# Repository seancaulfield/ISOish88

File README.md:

ISO(ish)88
==========

h88-compatible, F13 TKL with ISO support first (and no ANSI support)

* Uses RP2040 as microcontroller
* Hotswap supported
* Split left and right shift keys
* Bottom row is 7u/Tsangan (only, no ANSI support)

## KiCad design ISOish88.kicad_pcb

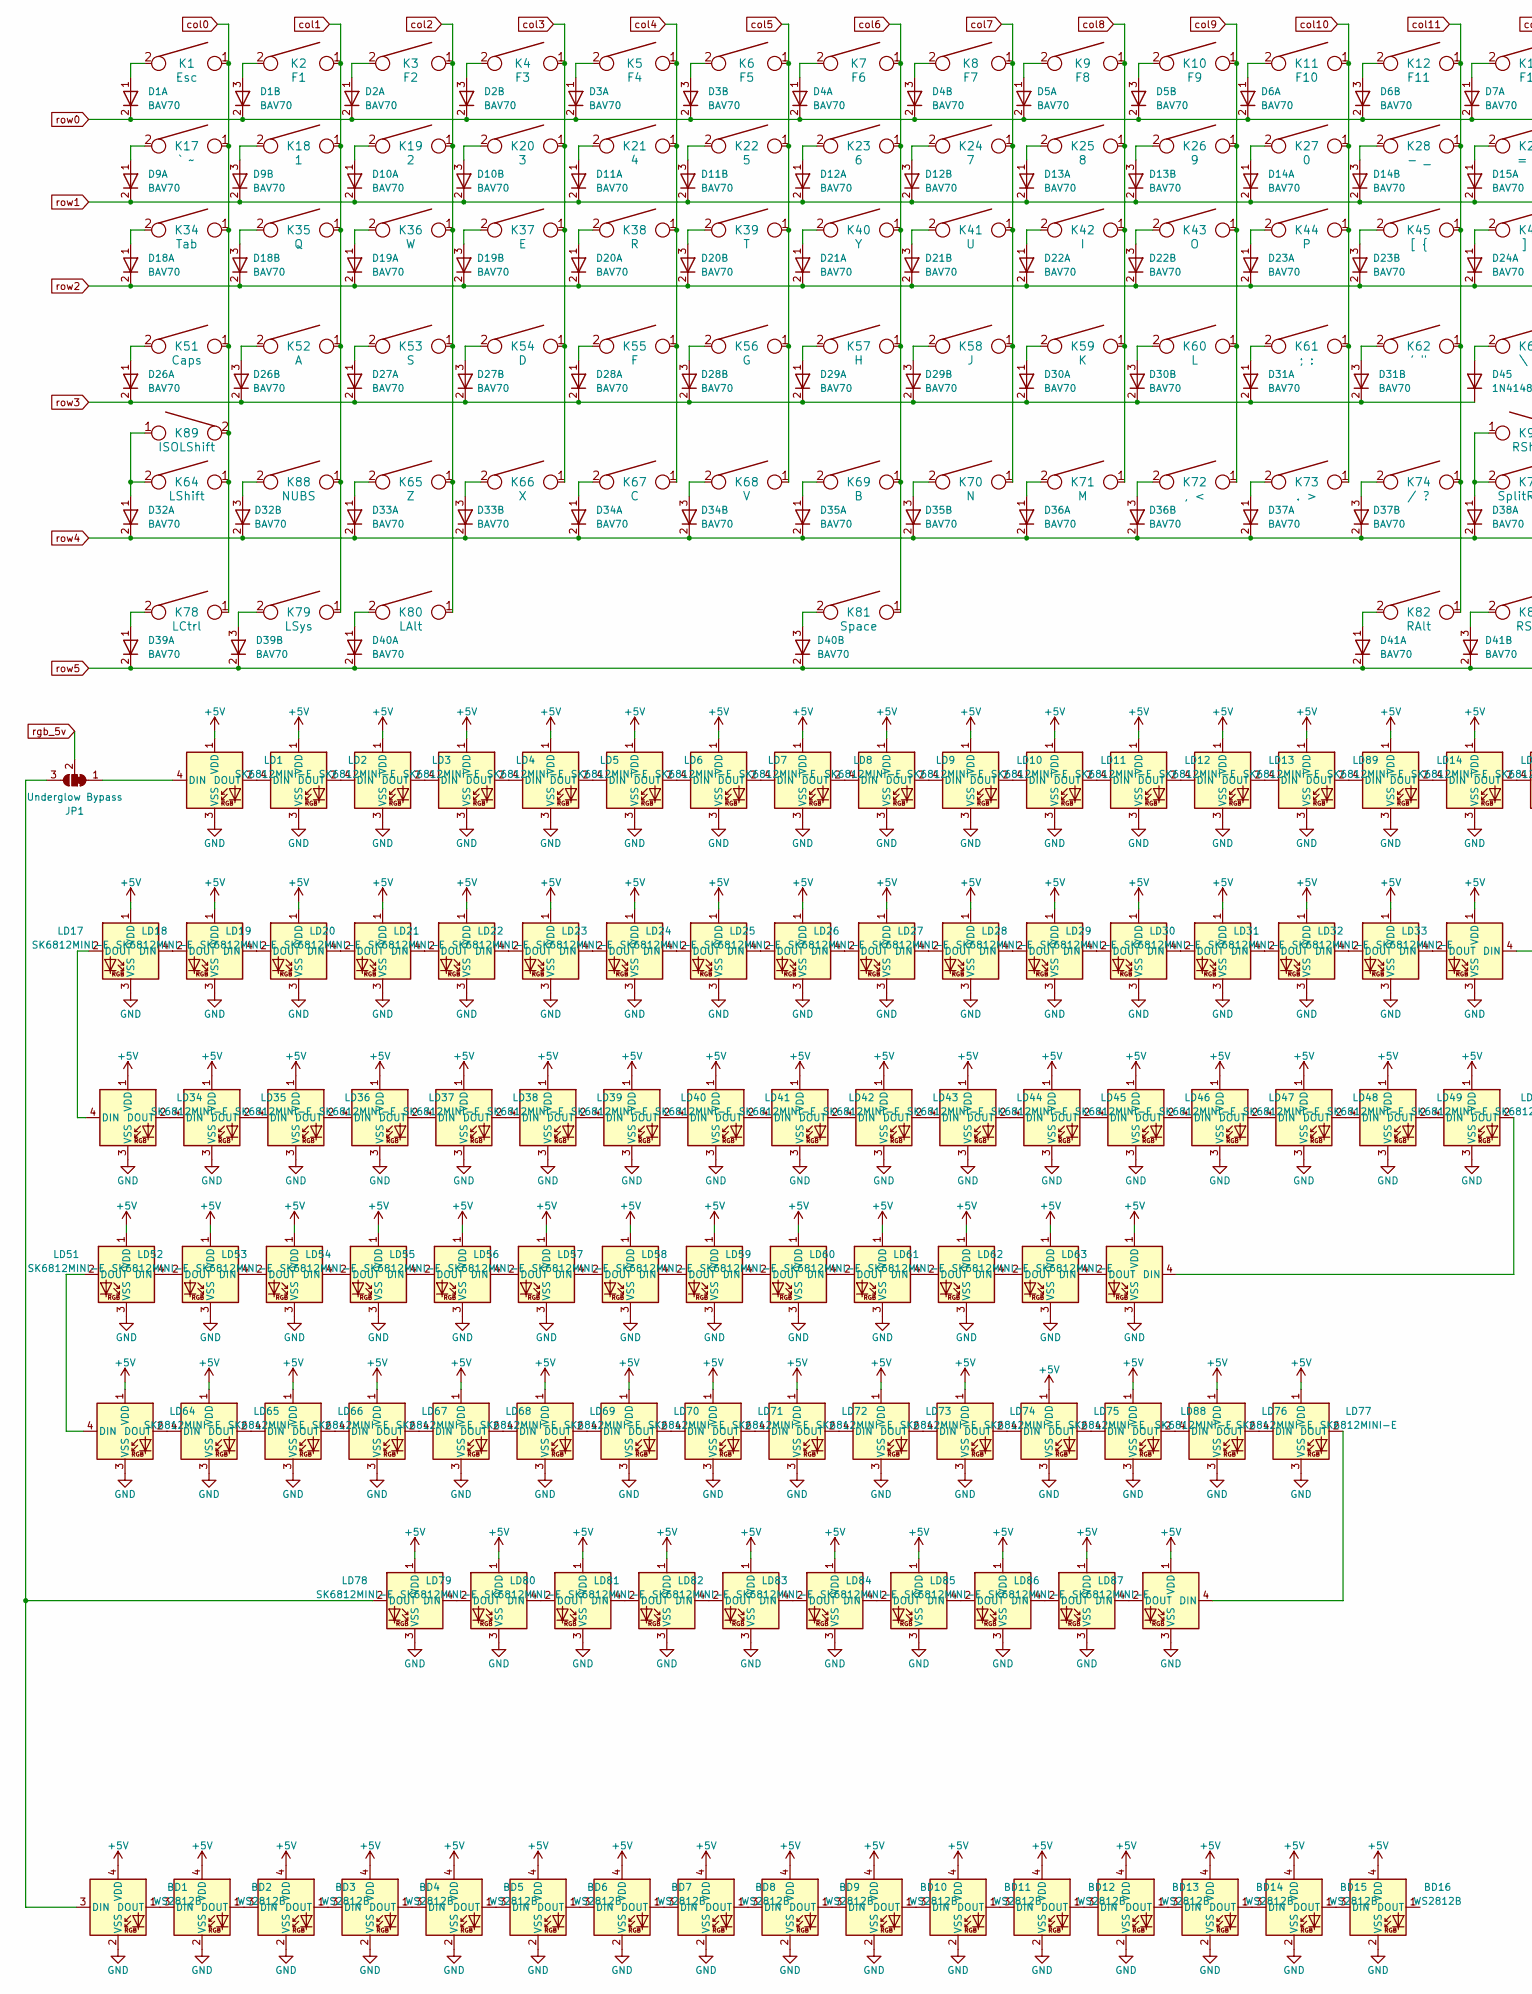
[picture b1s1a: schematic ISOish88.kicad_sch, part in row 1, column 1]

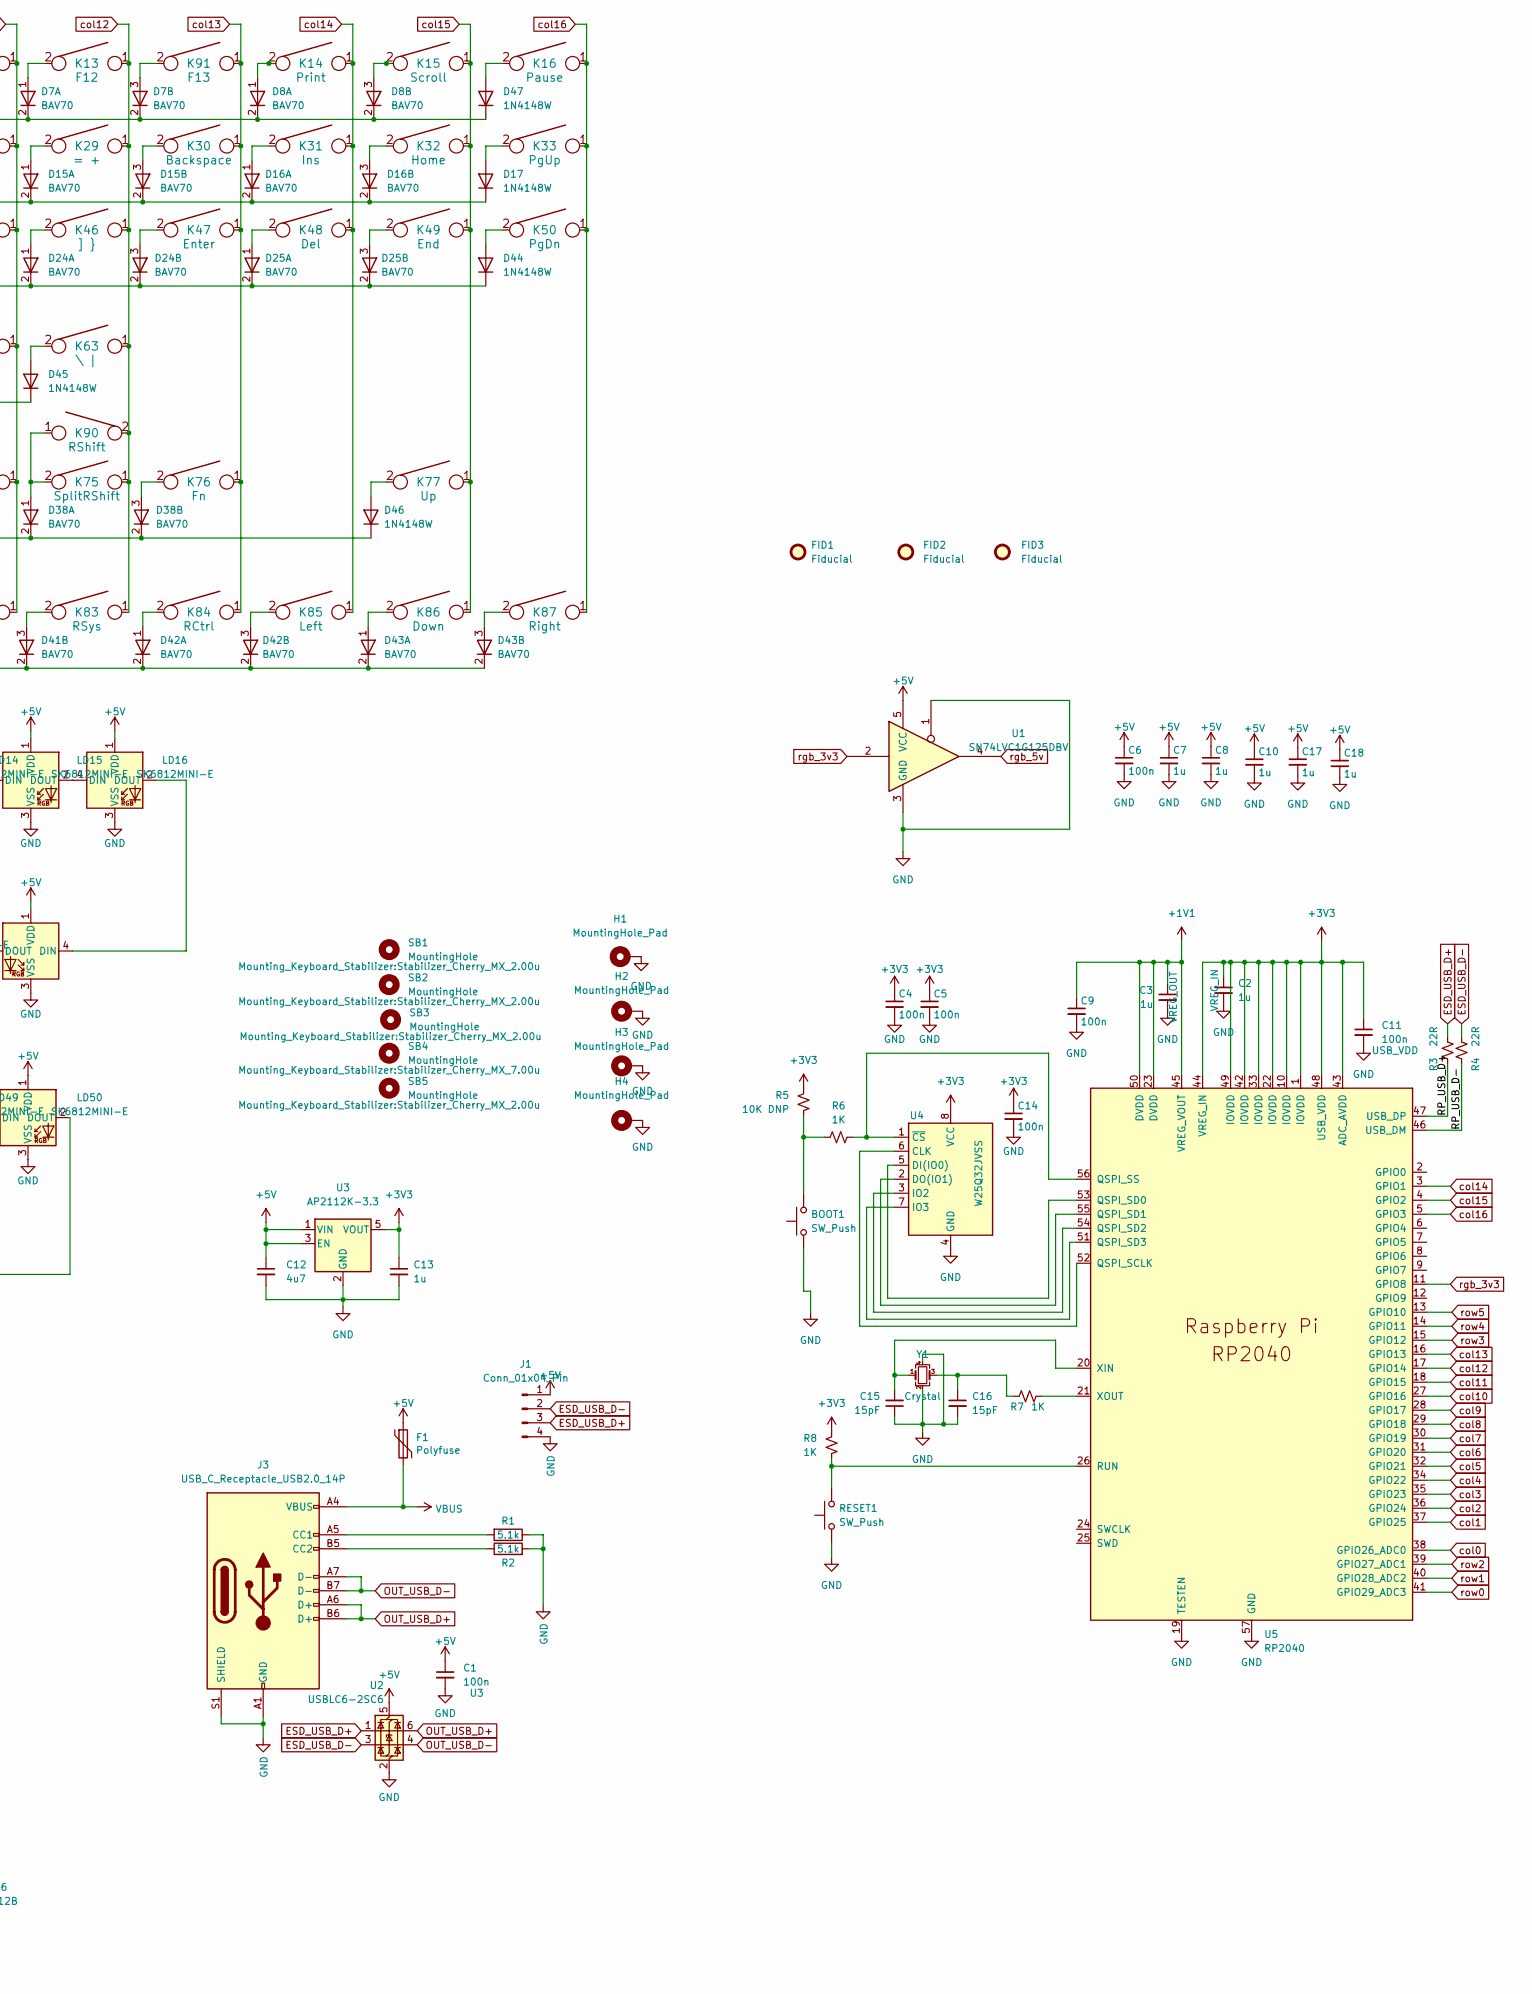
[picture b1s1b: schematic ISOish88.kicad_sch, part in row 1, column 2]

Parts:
BD1, BD2, BD3, BD4, BD5, BD6, BD7, BD8, BD9, BD10, BD11, BD12, BD13, BD14, BD15, BD16: WS2812B; LED_SK6812MINI_PLCC4_3.5x3.5mm_P1.75mm
BOOT1: SW_Push; SW_SPST_SKQG_WithStem
C1, C4, C5, C6, C9, C11, C14: 100n; C_0603_1608Metric
C2, C3, C7, C8, C10, C13, C17, C18: 1u; C_0603_1608Metric
C12: 4u7; C_0805_2012Metric
C15, C16: 15pF; C_0603_1608Metric
D1, D2, D3, D4, D5, D6, D7, D8, D9, D10, D11, D12, D13, D14, D15, D16, D18, D19, D20, D21, D22, D23, D24, D25, D26, D27, D28, D29, D30, D31, D32, D33, D34, D35, D36, D37, D38, D39, D40, D41, D42, D43: BAV70; SOT-23-1-3-2
D17, D44, D45, D46, D47: 1N4148W; D_SOD-123
F1: Polyfuse; R_1206_3216Metric
FID1: Fiducial; qmk_logo
FID2: Fiducial; OSHW-Logo_5.7x6mm_SilkScreen
FID3: Fiducial; COW
H1, H2, H3, H4: MountingHole_Pad; MountingHole_3.0mm_M2_5mm_dia_solderable
J1: Conn_01x04_Pin; JST_SH_SM04B-SRSS-TB_1x04-1MP_P1.00mm_Horizontal
J3: USB_C_Receptacle_USB2.0_14P; USB_C_Receptacle_GCT_USB4105-xx-A_16P_TopMnt_Horizontal
JP1: Underglow Bypass; SolderJumper-3_P1.3mm_Bridged12_RoundedPad1.0x1.5mm
K1: Esc; SW_Hotswap_Kailh_MX_1.00u
K2: F1; SW_Hotswap_Kailh_MX_1.00u
K3: F2; SW_Hotswap_Kailh_MX_1.00u
K4: F3; SW_Hotswap_Kailh_MX_1.00u
K5: F4; SW_Hotswap_Kailh_MX_1.00u
K6: F5; SW_Hotswap_Kailh_MX_1.00u
K7: F6; SW_Hotswap_Kailh_MX_1.00u
K8: F7; SW_Hotswap_Kailh_MX_1.00u
K9: F8; SW_Hotswap_Kailh_MX_1.00u
K10: F9; SW_Hotswap_Kailh_MX_1.00u
K11: F10; SW_Hotswap_Kailh_MX_1.00u
K12: F11; SW_Hotswap_Kailh_MX_1.00u
K13: F12; SW_Hotswap_Kailh_MX_1.00u
K14: Print; SW_Hotswap_Kailh_MX_1.00u
K15: Scroll; SW_Hotswap_Kailh_MX_1.00u
K16: Pause; SW_Hotswap_Kailh_MX_1.00u
K17: ` ~; SW_Hotswap_Kailh_MX_1.00u
K18: 1; SW_Hotswap_Kailh_MX_1.00u
K19: 2; SW_Hotswap_Kailh_MX_1.00u
K20: 3; SW_Hotswap_Kailh_MX_1.00u
K21: 4; SW_Hotswap_Kailh_MX_1.00u
K22: 5; SW_Hotswap_Kailh_MX_1.00u
K23: 6; SW_Hotswap_Kailh_MX_1.00u
K24: 7; SW_Hotswap_Kailh_MX_1.00u
K25: 8; SW_Hotswap_Kailh_MX_1.00u
K26: 9; SW_Hotswap_Kailh_MX_1.00u
K27: 0; SW_Hotswap_Kailh_MX_1.00u
K28: - _; SW_Hotswap_Kailh_MX_1.00u
K29: = +; SW_Hotswap_Kailh_MX_1.00u
K30: Backspace; SW_Hotswap_Kailh_MX_2.00u
K31: Ins; SW_Hotswap_Kailh_MX_1.00u
K32: Home; SW_Hotswap_Kailh_MX_1.00u
K33: PgUp; SW_Hotswap_Kailh_MX_1.00u
K34: Tab; SW_Hotswap_Kailh_MX_1.50u
K35: Q; SW_Hotswap_Kailh_MX_1.00u
K36: W; SW_Hotswap_Kailh_MX_1.00u
K37: E; SW_Hotswap_Kailh_MX_1.00u
K38: R; SW_Hotswap_Kailh_MX_1.00u
K39: T; SW_Hotswap_Kailh_MX_1.00u
K40: Y; SW_Hotswap_Kailh_MX_1.00u
K41: U; SW_Hotswap_Kailh_MX_1.00u
K42: I; SW_Hotswap_Kailh_MX_1.00u
K43: O; SW_Hotswap_Kailh_MX_1.00u
K44: P; SW_Hotswap_Kailh_MX_1.00u
K45: [ {; SW_Hotswap_Kailh_MX_1.00u
K46: ] }; SW_Hotswap_Kailh_MX_1.00u
K47: Enter; SW_Hotswap_Kailh_MX_ISOEnter
K48: Del; SW_Hotswap_Kailh_MX_1.00u
K49: End; SW_Hotswap_Kailh_MX_1.00u
K50: PgDn; SW_Hotswap_Kailh_MX_1.00u
K51: Caps; SW_Hotswap_Kailh_MX_1.25u
K52: A; SW_Hotswap_Kailh_MX_1.00u
K53: S; SW_Hotswap_Kailh_MX_1.00u
K54: D; SW_Hotswap_Kailh_MX_1.00u
K55: F; SW_Hotswap_Kailh_MX_1.00u
K56: G; SW_Hotswap_Kailh_MX_1.00u
K57: H; SW_Hotswap_Kailh_MX_1.00u
K58: J; SW_Hotswap_Kailh_MX_1.00u
K59: K; SW_Hotswap_Kailh_MX_1.00u
K60: L; SW_Hotswap_Kailh_MX_1.00u
K61: ; :; SW_Hotswap_Kailh_MX_1.00u
K62: ' "; SW_Hotswap_Kailh_MX_1.00u
K63: \ |; SW_Hotswap_Kailh_MX_1.00u
K64: LShift; SW_Hotswap_Kailh_MX_2.25u
K65: Z; SW_Hotswap_Kailh_MX_1.00u
K66: X; SW_Hotswap_Kailh_MX_1.00u
K67: C; SW_Hotswap_Kailh_MX_1.00u
K68: V; SW_Hotswap_Kailh_MX_1.00u
K69: B; SW_Hotswap_Kailh_MX_1.00u
K70: N; SW_Hotswap_Kailh_MX_1.00u
K71: M; SW_Hotswap_Kailh_MX_1.00u
K72: , <; SW_Hotswap_Kailh_MX_1.00u
K73: . >; SW_Hotswap_Kailh_MX_1.00u
K74: / ?; SW_Hotswap_Kailh_MX_1.00u
K75: SplitRShift; SW_Hotswap_Kailh_MX_1.75u
K76: Fn; SW_Hotswap_Kailh_MX_1.00u
K77: Up; SW_Hotswap_Kailh_MX_1.00u
K78: LCtrl; SW_Hotswap_Kailh_MX_1.50u
K79: LSys; SW_Hotswap_Kailh_MX_1.00u
K80: LAlt; SW_Hotswap_Kailh_MX_1.50u
K81: Space; SW_Hotswap_Kailh_MX_7.00u
K82: RAlt; SW_Hotswap_Kailh_MX_1.50u
K83: RSys; SW_Hotswap_Kailh_MX_1.00u
K84: RCtrl; SW_Hotswap_Kailh_MX_1.50u
K85: Left; SW_Hotswap_Kailh_MX_1.00u
K86: Down; SW_Hotswap_Kailh_MX_1.00u
K87: Right; SW_Hotswap_Kailh_MX_1.00u
K88: NUBS; SW_Hotswap_Kailh_MX_1.00u
K89: ISOLShift; SW_Hotswap_Kailh_MX_1.25u
K90: RShift; SW_Hotswap_Kailh_MX_2.75u
K91: F13; SW_Hotswap_Kailh_MX_1.00u
LD1, LD2, LD3, LD4, LD5, LD6, LD7, LD8, LD9, LD10, LD11, LD12, LD13, LD14, LD15, LD16, LD17, LD18, LD19, LD20, LD21, LD22, LD23, LD24, LD25, LD26, LD27, LD28, LD29, LD30, LD31, LD32, LD33, LD34, LD35, LD36, LD37, LD38, LD39, LD40, LD41, LD42, LD43, LD44, LD45, LD46, LD47, LD48, LD49, LD50, LD51, LD52, LD53, LD54, LD55, LD56, LD57, LD58, LD59, LD60, LD61, LD62, LD63, LD64, LD65, LD66, LD67, LD68, LD69, LD70, LD71, LD72, LD73, LD74, LD75, LD76, LD77, LD78, LD79, LD80, LD81, LD82, LD83, LD84, LD85, LD86, LD87, LD88, LD89: SK6812MINI-E; LED_SK6812MINI_PLCC4_3.1x2.7mm_P1.75mm_reverse_mount
R1, R2: 5.1k; R_0603_1608Metric
R3, R4: 22R; R_0603_1608Metric
R5: 10K DNP; R_0603_1608Metric
R6, R7, R8: 1K; R_0603_1608Metric
RESET1: SW_Push; SW_SPST_SKQG_WithStem
SB1, SB2, SB3, SB5: MountingHole; Stabilizer_Cherry_MX_2.00u
SB4: MountingHole; Stabilizer_Cherry_MX_7.00u
U1: SN74LVC1G125DBV; SOT-23-5
U2: USBLC6-2SC6; SOT-23-6
U3: AP2112K-3.3; SOT-23-5
U4: W25Q32JVSS; SOIC-8_5.23x5.23mm_P1.27mm
U5: RP2040; RP2040-QFN-56
Y1: Crystal; Crystal_SMD_3225-4Pin_3.2x2.5mm

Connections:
+1V1: C3.1, C9.1, U5.23 (DVDD), U5.45 (VREG_VOUT), U5.50 (DVDD)
+3V3: C2.1, C4.1, C5.1, C11.1, C13.1, C14.1, R5.2, R8.2, U3.5 (VOUT), U4.8 (VCC), U5.1 (IOVDD), U5.10 (IOVDD), U5.22 (IOVDD), U5.33 (IOVDD), U5.42 (IOVDD), U5.43 (ADC_AVDD), U5.44 (VREG_IN), U5.48 (USB_VDD), U5.49 (IOVDD)
+5V: BD1.4 (VDD), BD2.4 (VDD), BD3.4 (VDD), BD4.4 (VDD), BD5.4 (VDD), BD6.4 (VDD), BD7.4 (VDD), BD8.4 (VDD), BD9.4 (VDD), BD10.4 (VDD), BD11.4 (VDD), BD12.4 (VDD), BD13.4 (VDD), BD14.4 (VDD), BD15.4 (VDD), BD16.4 (VDD), C1.1, C6.1, C7.1, C8.1, C10.1, C12.1, C17.1, C18.1, F1.1, J1.1, LD1.1 (VDD), LD2.1 (VDD), LD3.1 (VDD), LD4.1 (VDD), LD5.1 (VDD), LD6.1 (VDD), LD7.1 (VDD), LD8.1 (VDD), LD9.1 (VDD), LD10.1 (VDD), LD11.1 (VDD), LD12.1 (VDD), LD13.1 (VDD), LD14.1 (VDD), LD15.1 (VDD), LD16.1 (VDD), LD17.1 (VDD), LD18.1 (VDD), LD19.1 (VDD), LD20.1 (VDD), LD21.1 (VDD), LD22.1 (VDD), LD23.1 (VDD), LD24.1 (VDD), LD25.1 (VDD), LD26.1 (VDD), LD27.1 (VDD), LD28.1 (VDD), LD29.1 (VDD), LD30.1 (VDD), LD31.1 (VDD), LD32.1 (VDD), LD33.1 (VDD), LD34.1 (VDD), LD35.1 (VDD), LD36.1 (VDD), LD37.1 (VDD), LD38.1 (VDD), LD39.1 (VDD), LD40.1 (VDD), LD41.1 (VDD), LD42.1 (VDD), LD43.1 (VDD), LD44.1 (VDD), LD45.1 (VDD), LD46.1 (VDD), LD47.1 (VDD), LD48.1 (VDD), LD49.1 (VDD), LD50.1 (VDD), LD51.1 (VDD), LD52.1 (VDD), LD53.1 (VDD), LD54.1 (VDD), LD55.1 (VDD), LD56.1 (VDD), LD57.1 (VDD), LD58.1 (VDD), LD59.1 (VDD), LD60.1 (VDD), LD61.1 (VDD), LD62.1 (VDD), LD63.1 (VDD), LD64.1 (VDD), LD65.1 (VDD), LD66.1 (VDD), LD67.1 (VDD), LD68.1 (VDD), LD69.1 (VDD), LD70.1 (VDD), LD71.1 (VDD), LD72.1 (VDD), LD73.1 (VDD), LD74.1 (VDD), LD75.1 (VDD), LD76.1 (VDD), LD77.1 (VDD), LD78.1 (VDD), LD79.1 (VDD), LD80.1 (VDD), LD81.1 (VDD), LD82.1 (VDD), LD83.1 (VDD), LD84.1 (VDD), LD85.1 (VDD), LD86.1 (VDD), LD87.1 (VDD), LD88.1 (VDD), LD89.1 (VDD), U1.5 (VCC), U2.5 (VBUS), U3.1 (VIN), U3.3 (EN)
/RP_USB_D+: R3.1, U5.47 (USB_DP)
/RP_USB_D-: R4.1, U5.46 (USB_DM)
ESD_USB_D+: J1.3, R3.2, U2.1 (I/O1)
ESD_USB_D-: J1.2, R4.2, U2.3 (I/O2)
GND: BD1.2 (VSS), BD2.2 (VSS), BD3.2 (VSS), BD4.2 (VSS), BD5.2 (VSS), BD6.2 (VSS), BD7.2 (VSS), BD8.2 (VSS), BD9.2 (VSS), BD10.2 (VSS), BD11.2 (VSS), BD12.2 (VSS), BD13.2 (VSS), BD14.2 (VSS), BD15.2 (VSS), BD16.2 (VSS), BOOT1.1, C1.2, C2.2, C3.2, C4.2, C5.2, C6.2, C7.2, C8.2, C9.2, C10.2, C11.2, C12.2, C13.2, C14.2, C15.1, C16.2, C17.2, C18.2, H1.1, H2.1, H3.1, H4.1, J1.4, J3.A1 (GND), J3.A12 (GND), J3.B1 (GND), J3.B12 (GND), J3.S1 (SHIELD), LD1.3 (VSS), LD2.3 (VSS), LD3.3 (VSS), LD4.3 (VSS), LD5.3 (VSS), LD6.3 (VSS), LD7.3 (VSS), LD8.3 (VSS), LD9.3 (VSS), LD10.3 (VSS), LD11.3 (VSS), LD12.3 (VSS), LD13.3 (VSS), LD14.3 (VSS), LD15.3 (VSS), LD16.3 (VSS), LD17.3 (VSS), LD18.3 (VSS), LD19.3 (VSS), LD20.3 (VSS), LD21.3 (VSS), LD22.3 (VSS), LD23.3 (VSS), LD24.3 (VSS), LD25.3 (VSS), LD26.3 (VSS), LD27.3 (VSS), LD28.3 (VSS), LD29.3 (VSS), LD30.3 (VSS), LD31.3 (VSS), LD32.3 (VSS), LD33.3 (VSS), LD34.3 (VSS), LD35.3 (VSS), LD36.3 (VSS), LD37.3 (VSS), LD38.3 (VSS), LD39.3 (VSS), LD40.3 (VSS), LD41.3 (VSS), LD42.3 (VSS), LD43.3 (VSS), LD44.3 (VSS), LD45.3 (VSS), LD46.3 (VSS), LD47.3 (VSS), LD48.3 (VSS), LD49.3 (VSS), LD50.3 (VSS), LD51.3 (VSS), LD52.3 (VSS), LD53.3 (VSS), LD54.3 (VSS), LD55.3 (VSS), LD56.3 (VSS), LD57.3 (VSS), LD58.3 (VSS), LD59.3 (VSS), LD60.3 (VSS), LD61.3 (VSS), LD62.3 (VSS), LD63.3 (VSS), LD64.3 (VSS), LD65.3 (VSS), LD66.3 (VSS), LD67.3 (VSS), LD68.3 (VSS), LD69.3 (VSS), LD70.3 (VSS), LD71.3 (VSS), LD72.3 (VSS), LD73.3 (VSS), LD74.3 (VSS), LD75.3 (VSS), LD76.3 (VSS), LD77.3 (VSS), LD78.3 (VSS), LD79.3 (VSS), LD80.3 (VSS), LD81.3 (VSS), LD82.3 (VSS), LD83.3 (VSS), LD84.3 (VSS), LD85.3 (VSS), LD86.3 (VSS), LD87.3 (VSS), LD88.3 (VSS), LD89.3 (VSS), R1.1, R2.2, RESET1.1, U1.1, U1.3 (GND), U2.2 (GND), U3.2 (GND), U4.4 (GND), U5.19 (TESTEN), U5.57 (GND), Y1.2, Y1.4
unnamed: BD1.3 (DIN), JP1.3 (B), LD78.2 (DOUT)
unnamed: BD1.1 (DOUT), BD2.3 (DIN)
unnamed: BD2.1 (DOUT), BD3.3 (DIN)
unnamed: BD3.1 (DOUT), BD4.3 (DIN)
unnamed: BD4.1 (DOUT), BD5.3 (DIN)
unnamed: BD5.1 (DOUT), BD6.3 (DIN)
unnamed: BD6.1 (DOUT), BD7.3 (DIN)
unnamed: BD7.1 (DOUT), BD8.3 (DIN)
unnamed: BD8.1 (DOUT), BD9.3 (DIN)
unnamed: BD9.1 (DOUT), BD10.3 (DIN)
unnamed: BD10.1 (DOUT), BD11.3 (DIN)
unnamed: BD11.1 (DOUT), BD12.3 (DIN)
unnamed: BD12.1 (DOUT), BD13.3 (DIN)
unnamed: BD13.1 (DOUT), BD14.3 (DIN)
unnamed: BD14.1 (DOUT), BD15.3 (DIN)
unnamed: BD15.1 (DOUT), BD16.3 (DIN)
unnamed: BOOT1.2, R5.1, R6.1
unnamed: C16.1, R7.2, Y1.3
unnamed: D1.1 (A), K1.2
unnamed: D1.3 (K), K2.2
unnamed: D2.1 (A), K3.2
unnamed: D2.3 (K), K4.2
unnamed: D3.1 (A), K5.2
unnamed: D3.3 (K), K6.2
unnamed: D4.1 (A), K7.2
unnamed: D4.3 (K), K8.2
unnamed: D5.1 (A), K9.2
unnamed: D5.3 (K), K10.2
unnamed: D6.1 (A), K11.2
unnamed: D6.3 (K), K12.2
unnamed: D7.1 (A), K13.2
unnamed: D7.3 (K), K91.2
unnamed: D8.1 (A), K14.2
unnamed: D8.3 (K), K15.2
unnamed: D9.1 (A), K17.2
unnamed: D9.3 (K), K18.2
unnamed: D10.1 (A), K19.2
unnamed: D10.3 (K), K20.2
unnamed: D11.1 (A), K21.2
unnamed: D11.3 (K), K22.2
unnamed: D12.1 (A), K23.2
unnamed: D12.3 (K), K24.2
unnamed: D13.1 (A), K25.2
unnamed: D13.3 (K), K26.2
unnamed: D14.1 (A), K27.2
unnamed: D14.3 (K), K28.2
unnamed: D15.1 (A), K29.2
unnamed: D15.3 (K), K30.2
unnamed: D16.1 (A), K31.2
unnamed: D16.3 (K), K32.2
unnamed: D17.2 (A), K33.2
unnamed: D18.1 (A), K34.2
unnamed: D18.3 (K), K35.2
unnamed: D19.1 (A), K36.2
unnamed: D19.3 (K), K37.2
unnamed: D20.1 (A), K38.2
unnamed: D20.3 (K), K39.2
unnamed: D21.1 (A), K40.2
unnamed: D21.3 (K), K41.2
unnamed: D22.1 (A), K42.2
unnamed: D22.3 (K), K43.2
unnamed: D23.1 (A), K44.2
unnamed: D23.3 (K), K45.2
unnamed: D24.1 (A), K46.2
unnamed: D24.3 (K), K47.2
unnamed: D25.1 (A), K48.2
unnamed: D25.3 (K), K49.2
unnamed: D26.1 (A), K51.2
unnamed: D26.3 (K), K52.2
unnamed: D27.1 (A), K53.2
unnamed: D27.3 (K), K54.2
unnamed: D28.1 (A), K55.2
unnamed: D28.3 (K), K56.2
unnamed: D29.1 (A), K57.2
unnamed: D29.3 (K), K58.2
unnamed: D30.1 (A), K59.2
unnamed: D30.3 (K), K60.2
unnamed: D31.1 (A), K61.2
unnamed: D31.3 (K), K62.2
unnamed: D32.1 (A), K64.2, K89.1
unnamed: D32.3 (K), K88.2
unnamed: D33.1 (A), K65.2
unnamed: D33.3 (K), K66.2
unnamed: D34.1 (A), K67.2
unnamed: D34.3 (K), K68.2
unnamed: D35.1 (A), K69.2
unnamed: D35.3 (K), K70.2
unnamed: D36.1 (A), K71.2
unnamed: D36.3 (K), K72.2
unnamed: D37.1 (A), K73.2
unnamed: D37.3 (K), K74.2
unnamed: D38.1 (A), K75.2, K90.1
unnamed: D38.3 (K), K76.2
unnamed: D39.1 (A), K78.2
unnamed: D39.3 (K), K79.2
unnamed: D40.1 (A), K80.2
unnamed: D40.3 (K), K81.2
unnamed: D41.1 (A), K82.2
unnamed: D41.3 (K), K83.2
unnamed: D42.1 (A), K84.2
unnamed: D42.3 (K), K85.2
unnamed: D43.1 (A), K86.2
unnamed: D43.3 (K), K87.2
unnamed: D44.2 (A), K50.2
unnamed: D45.2 (A), K63.2
unnamed: D46.2 (A), K77.2
unnamed: D47.2 (A), K16.2
unnamed: J3.A5 (CC1), R1.2
unnamed: J3.B5 (CC2), R2.1
unnamed: JP1.1 (A), LD1.4 (DIN)
unnamed: LD1.2 (DOUT), LD2.4 (DIN)
unnamed: LD2.2 (DOUT), LD3.4 (DIN)
unnamed: LD3.2 (DOUT), LD4.4 (DIN)
unnamed: LD4.2 (DOUT), LD5.4 (DIN)
unnamed: LD5.2 (DOUT), LD6.4 (DIN)
unnamed: LD6.2 (DOUT), LD7.4 (DIN)
unnamed: LD7.2 (DOUT), LD8.4 (DIN)
unnamed: LD8.2 (DOUT), LD9.4 (DIN)
unnamed: LD9.2 (DOUT), LD10.4 (DIN)
unnamed: LD10.2 (DOUT), LD11.4 (DIN)
unnamed: LD11.2 (DOUT), LD12.4 (DIN)
unnamed: LD12.2 (DOUT), LD13.4 (DIN)
unnamed: LD13.2 (DOUT), LD89.4 (DIN)
unnamed: LD14.4 (DIN), LD89.2 (DOUT)
unnamed: LD14.2 (DOUT), LD15.4 (DIN)
unnamed: LD15.2 (DOUT), LD16.4 (DIN)
unnamed: LD16.2 (DOUT), LD33.4 (DIN)
unnamed: LD17.4 (DIN), LD18.2 (DOUT)
unnamed: LD17.2 (DOUT), LD34.4 (DIN)
unnamed: LD18.4 (DIN), LD19.2 (DOUT)
unnamed: LD19.4 (DIN), LD20.2 (DOUT)
unnamed: LD20.4 (DIN), LD21.2 (DOUT)
unnamed: LD21.4 (DIN), LD22.2 (DOUT)
unnamed: LD22.4 (DIN), LD23.2 (DOUT)
unnamed: LD23.4 (DIN), LD24.2 (DOUT)
unnamed: LD24.4 (DIN), LD25.2 (DOUT)
unnamed: LD25.4 (DIN), LD26.2 (DOUT)
unnamed: LD26.4 (DIN), LD27.2 (DOUT)
unnamed: LD27.4 (DIN), LD28.2 (DOUT)
unnamed: LD28.4 (DIN), LD29.2 (DOUT)
unnamed: LD29.4 (DIN), LD30.2 (DOUT)
unnamed: LD30.4 (DIN), LD31.2 (DOUT)
unnamed: LD31.4 (DIN), LD32.2 (DOUT)
unnamed: LD32.4 (DIN), LD33.2 (DOUT)
unnamed: LD34.2 (DOUT), LD35.4 (DIN)
unnamed: LD35.2 (DOUT), LD36.4 (DIN)
unnamed: LD36.2 (DOUT), LD37.4 (DIN)
unnamed: LD37.2 (DOUT), LD38.4 (DIN)
unnamed: LD38.2 (DOUT), LD39.4 (DIN)
unnamed: LD39.2 (DOUT), LD40.4 (DIN)
unnamed: LD40.2 (DOUT), LD41.4 (DIN)
unnamed: LD41.2 (DOUT), LD42.4 (DIN)
unnamed: LD42.2 (DOUT), LD43.4 (DIN)
unnamed: LD43.2 (DOUT), LD44.4 (DIN)
unnamed: LD44.2 (DOUT), LD45.4 (DIN)
unnamed: LD45.2 (DOUT), LD46.4 (DIN)
unnamed: LD46.2 (DOUT), LD47.4 (DIN)
unnamed: LD47.2 (DOUT), LD48.4 (DIN)
unnamed: LD48.2 (DOUT), LD49.4 (DIN)
unnamed: LD49.2 (DOUT), LD50.4 (DIN)
unnamed: LD50.2 (DOUT), LD63.4 (DIN)
unnamed: LD51.4 (DIN), LD52.2 (DOUT)
unnamed: LD51.2 (DOUT), LD64.4 (DIN)
unnamed: LD52.4 (DIN), LD53.2 (DOUT)
unnamed: LD53.4 (DIN), LD54.2 (DOUT)
unnamed: LD54.4 (DIN), LD55.2 (DOUT)
unnamed: LD55.4 (DIN), LD56.2 (DOUT)
unnamed: LD56.4 (DIN), LD57.2 (DOUT)
unnamed: LD57.4 (DIN), LD58.2 (DOUT)
unnamed: LD58.4 (DIN), LD59.2 (DOUT)
unnamed: LD59.4 (DIN), LD60.2 (DOUT)
unnamed: LD60.4 (DIN), LD61.2 (DOUT)
unnamed: LD61.4 (DIN), LD62.2 (DOUT)
unnamed: LD62.4 (DIN), LD63.2 (DOUT)
unnamed: LD64.2 (DOUT), LD65.4 (DIN)
unnamed: LD65.2 (DOUT), LD66.4 (DIN)
unnamed: LD66.2 (DOUT), LD67.4 (DIN)
unnamed: LD67.2 (DOUT), LD68.4 (DIN)
unnamed: LD68.2 (DOUT), LD69.4 (DIN)
unnamed: LD69.2 (DOUT), LD70.4 (DIN)
unnamed: LD70.2 (DOUT), LD71.4 (DIN)
unnamed: LD71.2 (DOUT), LD72.4 (DIN)
unnamed: LD72.2 (DOUT), LD73.4 (DIN)
unnamed: LD73.2 (DOUT), LD74.4 (DIN)
unnamed: LD74.2 (DOUT), LD75.4 (DIN)
unnamed: LD75.2 (DOUT), LD88.4 (DIN)
unnamed: LD76.4 (DIN), LD88.2 (DOUT)
unnamed: LD76.2 (DOUT), LD77.4 (DIN)
unnamed: LD77.2 (DOUT), LD87.4 (DIN)
unnamed: LD78.4 (DIN), LD79.2 (DOUT)
unnamed: LD79.4 (DIN), LD80.2 (DOUT)
unnamed: LD80.4 (DIN), LD81.2 (DOUT)
unnamed: LD81.4 (DIN), LD82.2 (DOUT)
unnamed: LD82.4 (DIN), LD83.2 (DOUT)
unnamed: LD83.4 (DIN), LD84.2 (DOUT)
unnamed: LD84.4 (DIN), LD85.2 (DOUT)
unnamed: LD85.4 (DIN), LD86.2 (DOUT)
unnamed: LD86.4 (DIN), LD87.2 (DOUT)
unnamed: U4.6 (CLK), U5.52 (QSPI_SCLK)
unnamed: U4.5 (DI(IO0)), U5.53 (QSPI_SD0)
unnamed: U4.2 (DO(IO1)), U5.55 (QSPI_SD1)
unnamed: U4.3 (IO2), U5.54 (QSPI_SD2)
unnamed: U4.7 (IO3), U5.51 (QSPI_SD3)
unnamed: R6.2, U4.1 (~CS), U5.56 (QSPI_SS)
unnamed: R8.1, RESET1.2, U5.26 (RUN)
unnamed: C15.2, U5.20 (XIN), Y1.1
unnamed: R7.1, U5.21 (XOUT)
OUT_USB_D+: J3.A6 (D+), J3.B6 (D+), U2.6 (I/O1)
OUT_USB_D-: J3.A7 (D-), J3.B7 (D-), U2.4 (I/O2)
VBUS: F1.2, J3.A4 (VBUS), J3.A9 (VBUS), J3.B4 (VBUS), J3.B9 (VBUS)
col0: K1.1, K17.1, K34.1, K51.1, K64.1, K78.1, K89.2, U5.38 (GPIO26_ADC0)
col1: K2.1, K18.1, K35.1, K52.1, K79.1, K88.1, U5.37 (GPIO25)
col2: K3.1, K19.1, K36.1, K53.1, K65.1, K80.1, U5.36 (GPIO24)
col3: K4.1, K20.1, K37.1, K54.1, K66.1, U5.35 (GPIO23)
col4: K5.1, K21.1, K38.1, K55.1, K67.1, U5.34 (GPIO22)
col5: K6.1, K22.1, K39.1, K56.1, K68.1, U5.32 (GPIO21)
col6: K7.1, K23.1, K40.1, K57.1, K69.1, K81.1, U5.31 (GPIO20)
col7: K8.1, K24.1, K41.1, K58.1, K70.1, U5.30 (GPIO19)
col8: K9.1, K25.1, K42.1, K59.1, K71.1, U5.29 (GPIO18)
col9: K10.1, K26.1, K43.1, K60.1, K72.1, U5.28 (GPIO17)
col10: K11.1, K27.1, K44.1, K61.1, K73.1, U5.27 (GPIO16)
col11: K12.1, K28.1, K45.1, K62.1, K74.1, K82.1, U5.18 (GPIO15)
col12: K13.1, K29.1, K46.1, K63.1, K75.1, K83.1, K90.2, U5.17 (GPIO14)
col13: K30.1, K47.1, K76.1, K84.1, K91.1, U5.16 (GPIO13)
col14: K14.1, K31.1, K48.1, K85.1, U5.3 (GPIO1)
col15: K15.1, K32.1, K49.1, K77.1, K86.1, U5.4 (GPIO2)
col16: K16.1, K33.1, K50.1, K87.1, U5.5 (GPIO3)
rgb_3v3: U1.2, U5.11 (GPIO8)
rgb_5v: JP1.2 (C), U1.4
row0: D1.2 (K), D2.2 (K), D3.2 (K), D4.2 (K), D5.2 (K), D6.2 (K), D7.2 (K), D8.2 (K), D47.1 (K), U5.41 (GPIO29_ADC3)
row1: D9.2 (K), D10.2 (K), D11.2 (K), D12.2 (K), D13.2 (K), D14.2 (K), D15.2 (K), D16.2 (K), D17.1 (K), U5.40 (GPIO28_ADC2)
row2: D18.2 (K), D19.2 (K), D20.2 (K), D21.2 (K), D22.2 (K), D23.2 (K), D24.2 (K), D25.2 (K), D44.1 (K), U5.39 (GPIO27_ADC1)
row3: D26.2 (K), D27.2 (K), D28.2 (K), D29.2 (K), D30.2 (K), D31.2 (K), D45.1 (K), U5.15 (GPIO12)
row4: D32.2 (K), D33.2 (K), D34.2 (K), D35.2 (K), D36.2 (K), D37.2 (K), D38.2 (K), D46.1 (K), U5.14 (GPIO11)
row5: D39.2 (K), D40.2 (K), D41.2 (K), D42.2 (K), D43.2 (K), U5.13 (GPIO10)

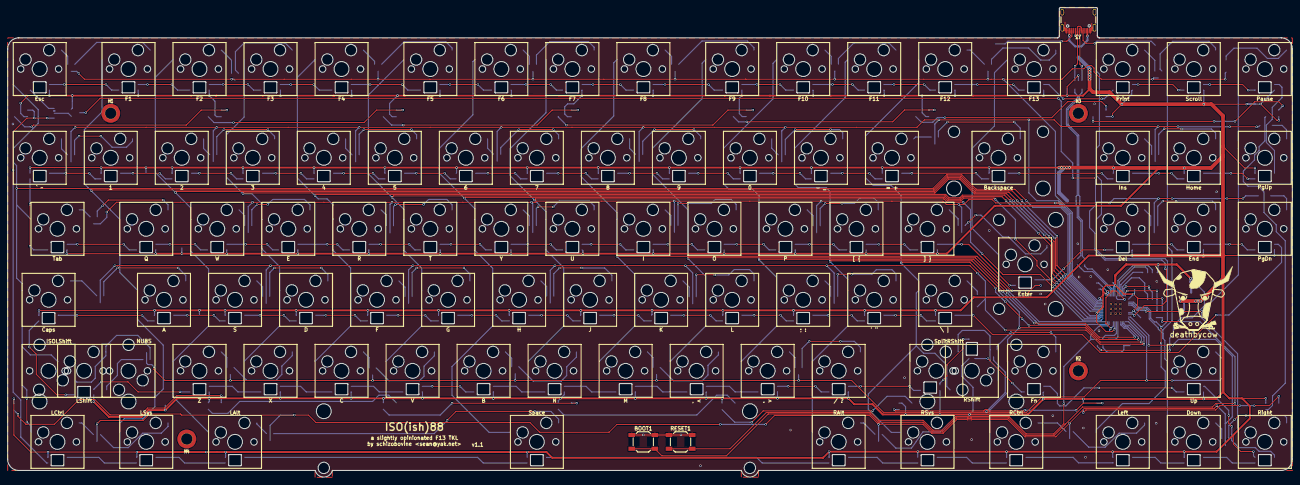
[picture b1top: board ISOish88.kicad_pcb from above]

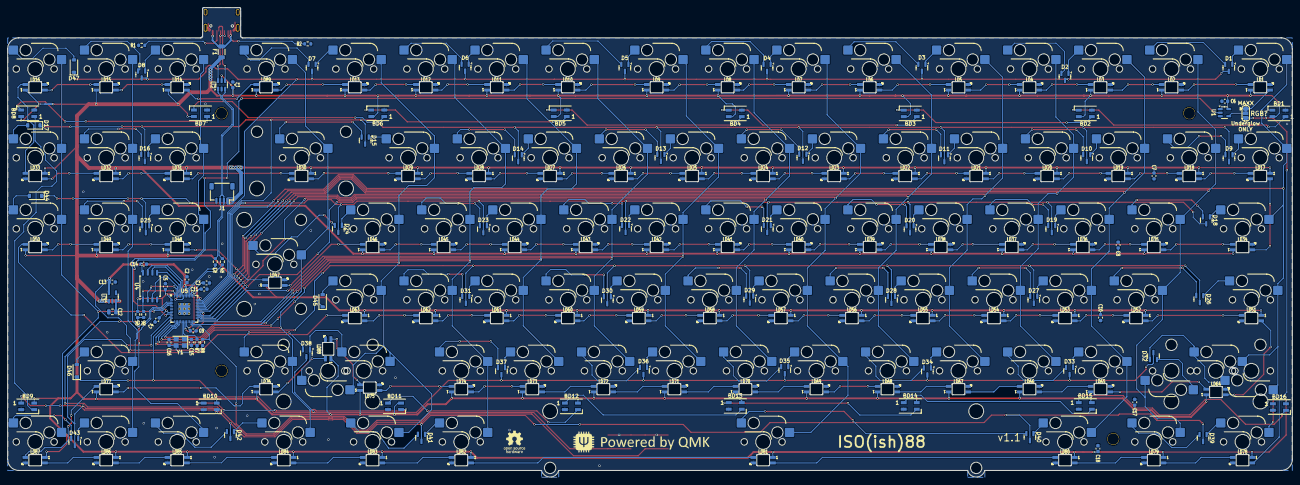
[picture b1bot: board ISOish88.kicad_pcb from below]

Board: 2 copper layers, 344.6 x 125.9 mm, 293 parts (100 on the bottom side), 243 nets.

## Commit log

2026-05-26 initial f13 revision
2026-05-26 add readme
2026-05-26 more RGB footprint fixes
2026-06-15 tweaks
